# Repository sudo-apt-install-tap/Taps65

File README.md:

# Taps65 ⌨️

<div align="center">  ⚠️ <b> This project is deprecated. </b>  
Please check out <b> Tap65 V2 </b> for the current handwired version. </div> <br>

A custom mechanical keyboard project designed to replace my current daily driver.  
Not a showpiece. Not a concept. Something I can actually use every day.

This project documents the full process of designing and building a keyboard from scratch, following **ai03’s keyboard design guide** as a reference.

---

## 📌 About the Project

Taps65 is a personal keyboard project focused on:
- Practical daily usability
- Clean and understandable design
- Learning proper keyboard PCB design workflows

I’m aiming for something reliable, simple, and functional—no unnecessary fluff.

If you’re following along and something doesn’t make sense, ai03’s guide is highly recommended. It explains the fundamentals far better than I can.

---

## 📷 Images

<br> - MCU Schematic  <br>

<br> - USB-C Schematic <br>

<br> - PCB Front <br>

<br> - PCB Back <br>

<br> - PCB Assembled <br>

---

## 🚧 Planned Work

- Add USB protection components ✔
- Key matrix design ✔
- PCB layout ✔
- Plate and case design 
- Firmware (QMK)
- Prototyping and testing

---

## 🤝 Get in Touch

If you want help building your own keyboard or have questions about this project:

### Slack: **@taps**
### Email: **work.tapishnud@gmail.com**

---

## ⚠️ Disclaimer

This is a learning project. Things may break, change, or be redesigned multiple times.  
That’s part of the process.

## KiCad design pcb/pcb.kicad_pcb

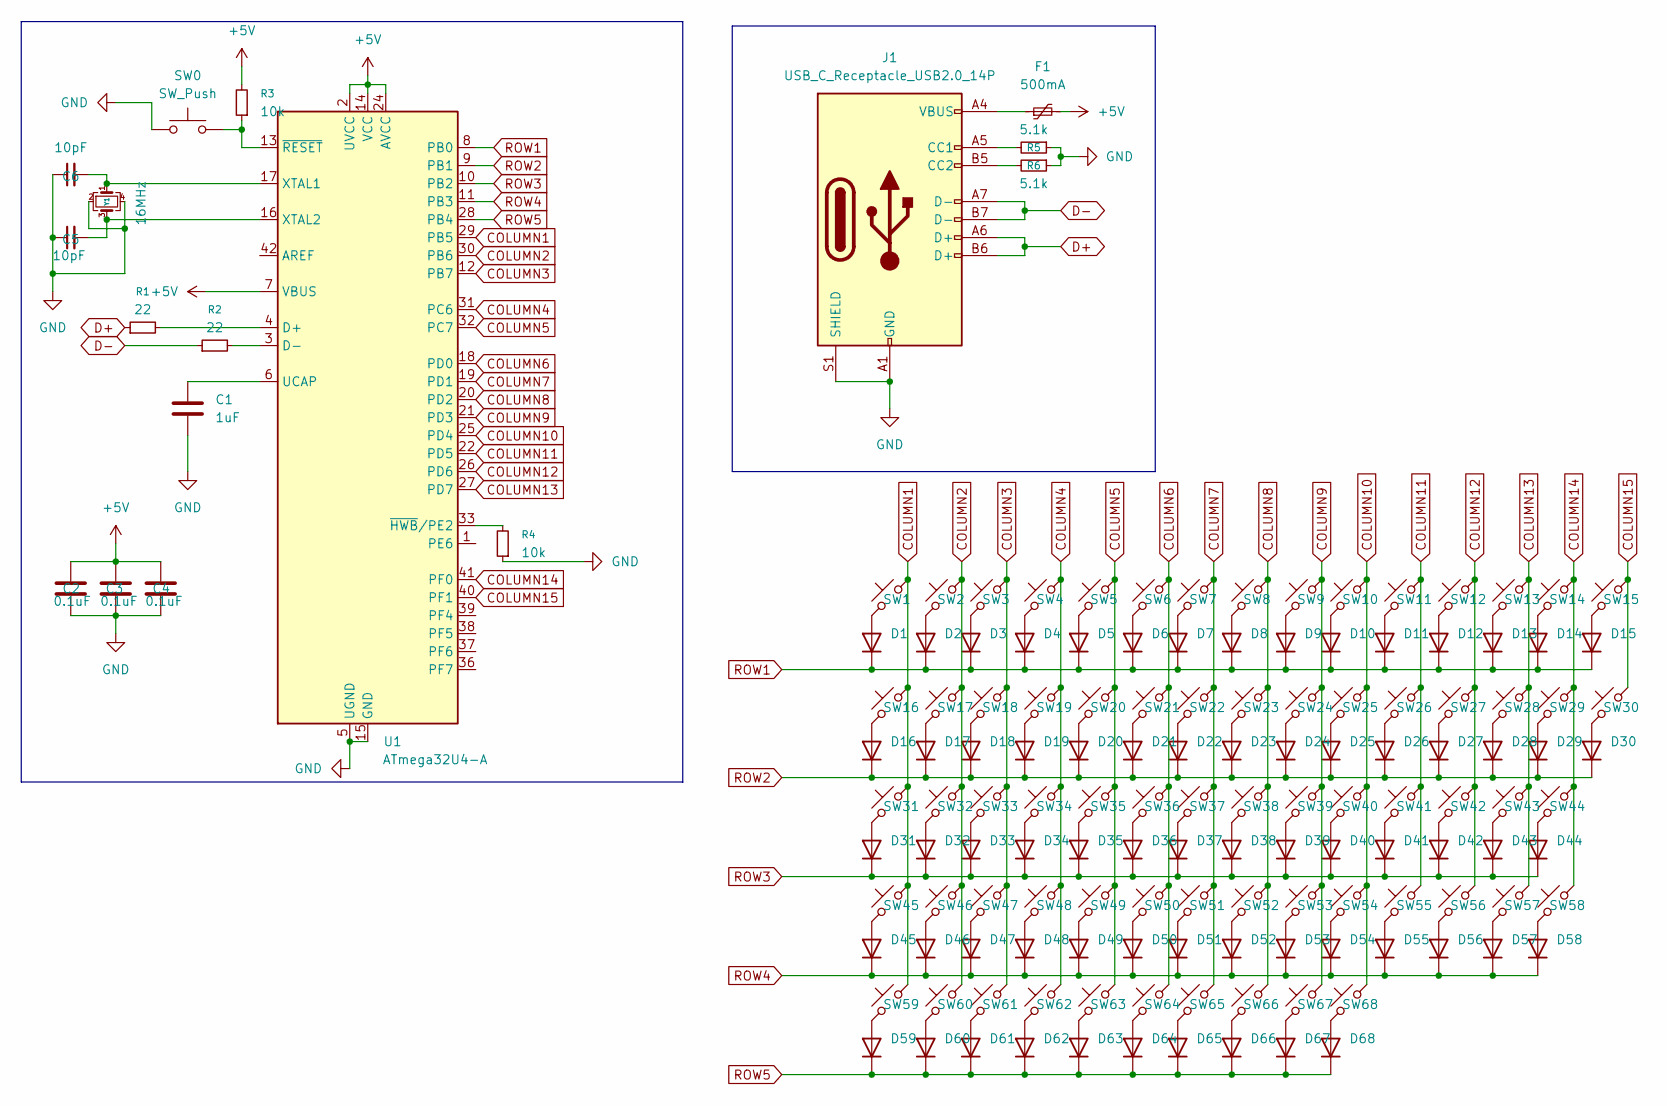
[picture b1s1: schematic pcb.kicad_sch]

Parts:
C1: 1uF; C_0805_2012Metric
C2, C3, C4: 0.1uF; C_0805_2012Metric
C5, C6: 10pF; C_0805_2012Metric
D1, D2, D3, D4, D5, D6, D7, D8, D9, D10, D11, D12, D13, D14, D15, D16, D17, D18, D19, D20, D21, D22, D23, D24, D25, D26, D27, D28, D29, D30, D31, D32, D33, D34, D35, D36, D37, D38, D39, D40, D41, D42, D43, D44, D45, D46, D47, D48, D49, D50, D51, D52, D53, D54, D55, D56, D57, D58, D59, D60, D61, D62, D63, D64, D65, D66, D67, D68: 1N4148WT; D_SOD-123
F1: 500mA; Fuse_1206_3216Metric
J1: USB_C_Receptacle_USB2.0_14P; USB_C_Receptacle_HRO_TYPE-C-31-M-17
R1, R2: 22; R_0805_2012Metric
R3, R4: 10k; R_0805_2012Metric
R5, R6: 5.1k; R_0805_2012Metric
SW0: SW_Push; SW_SPST_B3S-1000
SW1, SW2, SW3, SW4, SW5, SW6, SW7, SW8, SW9, SW10, SW11, SW12, SW13, SW14, SW17, SW18, SW19, SW20, SW21, SW22, SW23, SW24, SW25, SW26, SW27, SW28, SW29, SW32, SW33, SW34, SW35, SW36, SW37, SW38, SW39, SW40, SW41, SW42, SW43, SW46, SW47, SW48, SW49, SW50, SW51, SW52, SW53, SW54, SW55, SW57, SW58, SW66, SW67, SW68: SW_Push_45deg; SW_Cherry_MX_1.00u_PCB
SW15: SW_Push_45deg; SW_Cherry_MX_2.00u_PCB
SW16, SW30: SW_Push_45deg; SW_Cherry_MX_1.50u_PCB
SW31, SW56: SW_Push_45deg; SW_Cherry_MX_1.75u_PCB
SW44, SW45: SW_Push_45deg; SW_Cherry_MX_2.25u_PCB
SW59, SW60, SW61: SW_Push_45deg; SW_Cherry_MX_1.25u_PCB
SW62: SW_Push_45deg; SW_Cherry_MX_6.25u_PCB
SW63, SW64, SW65: SW_Push_45deg; SW_Cherry_MX_1.00u_Plate
U1: ATmega32U4-A; TQFP-44_10x10mm_P0.8mm
Y1: 16MHz; Crystal_SMD_3225-4Pin_3.2x2.5mm

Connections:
+5V: C2.1, C3.1, C4.1, F1.2, R3.2, U1.2 (UVCC), U1.7 (VBUS), U1.14 (VCC), U1.24 (AVCC), U1.34 (VCC), U1.44 (AVCC)
COLUMN1: SW1.2, SW16.2, SW31.2, SW45.2, SW59.2, U1.29 (PB5)
COLUMN2: SW2.2, SW17.2, SW32.2, SW46.2, SW60.2, U1.30 (PB6)
COLUMN3: SW3.2, SW18.2, SW33.2, SW47.2, SW61.2, U1.12 (PB7)
COLUMN4: SW4.2, SW19.2, SW34.2, SW48.2, SW62.2, U1.31 (PC6)
COLUMN5: SW5.2, SW20.2, SW35.2, SW49.2, SW63.2, U1.32 (PC7)
COLUMN6: SW6.2, SW21.2, SW36.2, SW50.2, SW64.2, U1.18 (PD0)
COLUMN7: SW7.2, SW22.2, SW37.2, SW51.2, SW65.2, U1.19 (PD1)
COLUMN8: SW8.2, SW23.2, SW38.2, SW52.2, SW66.2, U1.20 (PD2)
COLUMN9: SW9.2, SW24.2, SW39.2, SW53.2, SW67.2, U1.21 (PD3)
COLUMN10: SW10.2, SW25.2, SW40.2, SW54.2, SW68.2, U1.25 (PD4)
COLUMN11: SW11.2, SW26.2, SW41.2, SW55.2, U1.22 (PD5)
COLUMN12: SW12.2, SW27.2, SW42.2, SW56.2, U1.26 (PD6)
COLUMN13: SW13.2, SW28.2, SW43.2, SW57.2, U1.27 (PD7)
COLUMN14: SW14.2, SW29.2, SW44.2, SW58.2, U1.41 (PF0)
COLUMN15: SW15.2, SW30.2, U1.40 (PF1)
D+: J1.A6 (D+), J1.B6 (D+), R1.1
D-: J1.A7 (D-), J1.B7 (D-), R2.1
GND: C1.2, C2.2, C3.2, C4.2, C5.1, C6.1, J1.A1 (GND), J1.A12 (GND), J1.B1 (GND), J1.B12 (GND), J1.S1 (SHIELD), R4.1, R5.1, R6.1, SW0.1, U1.5 (UGND), U1.15 (GND), U1.23 (GND), U1.35 (GND), U1.43 (GND), Y1.2, Y1.4
unnamed: D1.2 (A), SW1.1
unnamed: D2.2 (A), SW2.1
unnamed: D3.2 (A), SW3.1
unnamed: D4.2 (A), SW4.1
unnamed: D5.2 (A), SW5.1
unnamed: D6.2 (A), SW6.1
unnamed: D7.2 (A), SW7.1
unnamed: D8.2 (A), SW8.1
unnamed: D9.2 (A), SW9.1
unnamed: D10.2 (A), SW10.1
unnamed: D11.2 (A), SW11.1
unnamed: D12.2 (A), SW12.1
unnamed: D13.2 (A), SW13.1
unnamed: D14.2 (A), SW14.1
unnamed: D15.2 (A), SW15.1
unnamed: D16.2 (A), SW16.1
unnamed: D17.2 (A), SW17.1
unnamed: D18.2 (A), SW18.1
unnamed: D19.2 (A), SW19.1
unnamed: D20.2 (A), SW20.1
unnamed: D21.2 (A), SW21.1
unnamed: D22.2 (A), SW22.1
unnamed: D23.2 (A), SW23.1
unnamed: D24.2 (A), SW24.1
unnamed: D25.2 (A), SW25.1
unnamed: D26.2 (A), SW26.1
unnamed: D27.2 (A), SW27.1
unnamed: D28.2 (A), SW28.1
unnamed: D29.2 (A), SW29.1
unnamed: D30.2 (A), SW30.1
unnamed: D31.2 (A), SW31.1
unnamed: D32.2 (A), SW32.1
unnamed: D33.2 (A), SW33.1
unnamed: D34.2 (A), SW34.1
unnamed: D35.2 (A), SW35.1
unnamed: D36.2 (A), SW36.1
unnamed: D37.2 (A), SW37.1
unnamed: D38.2 (A), SW38.1
unnamed: D39.2 (A), SW39.1
unnamed: D40.2 (A), SW40.1
unnamed: D41.2 (A), SW41.1
unnamed: D42.2 (A), SW42.1
unnamed: D43.2 (A), SW43.1
unnamed: D44.2 (A), SW44.1
unnamed: D45.2 (A), SW45.1
unnamed: D46.2 (A), SW46.1
unnamed: D47.2 (A), SW47.1
unnamed: D48.2 (A), SW48.1
unnamed: D49.2 (A), SW49.1
unnamed: D50.2 (A), SW50.1
unnamed: D51.2 (A), SW51.1
unnamed: D52.2 (A), SW52.1
unnamed: D53.2 (A), SW53.1
unnamed: D54.2 (A), SW54.1
unnamed: D55.2 (A), SW55.1
unnamed: D56.2 (A), SW56.1
unnamed: D57.2 (A), SW57.1
unnamed: D58.2 (A), SW58.1
unnamed: D59.2 (A), SW59.1
unnamed: D60.2 (A), SW60.1
unnamed: D61.2 (A), SW61.1
unnamed: D62.2 (A), SW62.1
unnamed: D63.2 (A), SW63.1
unnamed: D64.2 (A), SW64.1
unnamed: D65.2 (A), SW65.1
unnamed: D66.2 (A), SW66.1
unnamed: D67.2 (A), SW67.1
unnamed: D68.2 (A), SW68.1
unnamed: F1.1, J1.A4 (VBUS), J1.A9 (VBUS), J1.B4 (VBUS), J1.B9 (VBUS)
unnamed: J1.A5 (CC1), R5.2
unnamed: J1.B5 (CC2), R6.2
unnamed: R1.2, U1.4 (D+)
unnamed: R2.2, U1.3 (D-)
unnamed: C1.1, U1.6 (UCAP)
unnamed: C6.2, U1.17 (XTAL1), Y1.1
unnamed: C5.2, U1.16 (XTAL2), Y1.3
unnamed: R4.2, U1.33 (~HWB/PE2)
unnamed: R3.1, SW0.2, U1.13 (~RESET)
ROW1: D1.1 (K), D2.1 (K), D3.1 (K), D4.1 (K), D5.1 (K), D6.1 (K), D7.1 (K), D8.1 (K), D9.1 (K), D10.1 (K), D11.1 (K), D12.1 (K), D13.1 (K), D14.1 (K), D15.1 (K), U1.8 (PB0)
ROW2: D16.1 (K), D17.1 (K), D18.1 (K), D19.1 (K), D20.1 (K), D21.1 (K), D22.1 (K), D23.1 (K), D24.1 (K), D25.1 (K), D26.1 (K), D27.1 (K), D28.1 (K), D29.1 (K), D30.1 (K), U1.9 (PB1)
ROW3: D31.1 (K), D32.1 (K), D33.1 (K), D34.1 (K), D35.1 (K), D36.1 (K), D37.1 (K), D38.1 (K), D39.1 (K), D40.1 (K), D41.1 (K), D42.1 (K), D43.1 (K), D44.1 (K), U1.10 (PB2)
ROW4: D45.1 (K), D46.1 (K), D47.1 (K), D48.1 (K), D49.1 (K), D50.1 (K), D51.1 (K), D52.1 (K), D53.1 (K), D54.1 (K), D55.1 (K), D56.1 (K), D57.1 (K), D58.1 (K), U1.11 (PB3)
ROW5: D59.1 (K), D60.1 (K), D61.1 (K), D62.1 (K), D63.1 (K), D64.1 (K), D65.1 (K), D66.1 (K), D67.1 (K), D68.1 (K), U1.28 (PB4)

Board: 2 copper layers, 153 parts (5 on the bottom side), 100 nets, no tracks yet.

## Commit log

2026-01-14 added README.MD
2026-01-14 Add README for Taps65 mechanical keyboard project
    This README documents the Taps65 mechanical keyboard project, outlining its purpose, design focus, planned work, and contact information.
2026-01-14 Added PCB Layout
2026-01-16 Added Images - Finished Routing - Added silkscreen
2026-01-16 Update README with additional PCB images
    Added additional images of PCB front and back to the README.
2026-01-16 Rerouted - New Layout
2026-01-23 Updated Images
2026-01-23 Revise README with new images and project information
    Updated README to include additional images and project details.
2026-01-23 Revise README with project updates and contact info
    Updated project details, added planned work status, and clarified contact information.
2026-03-12 Mark Taps65 as deprecated and reference Tap65 V2
    Updated README to indicate project deprecation and direct users to Tap65 V2.
